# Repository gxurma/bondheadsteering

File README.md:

# bondheadsteering
App to steer a heated bondhead

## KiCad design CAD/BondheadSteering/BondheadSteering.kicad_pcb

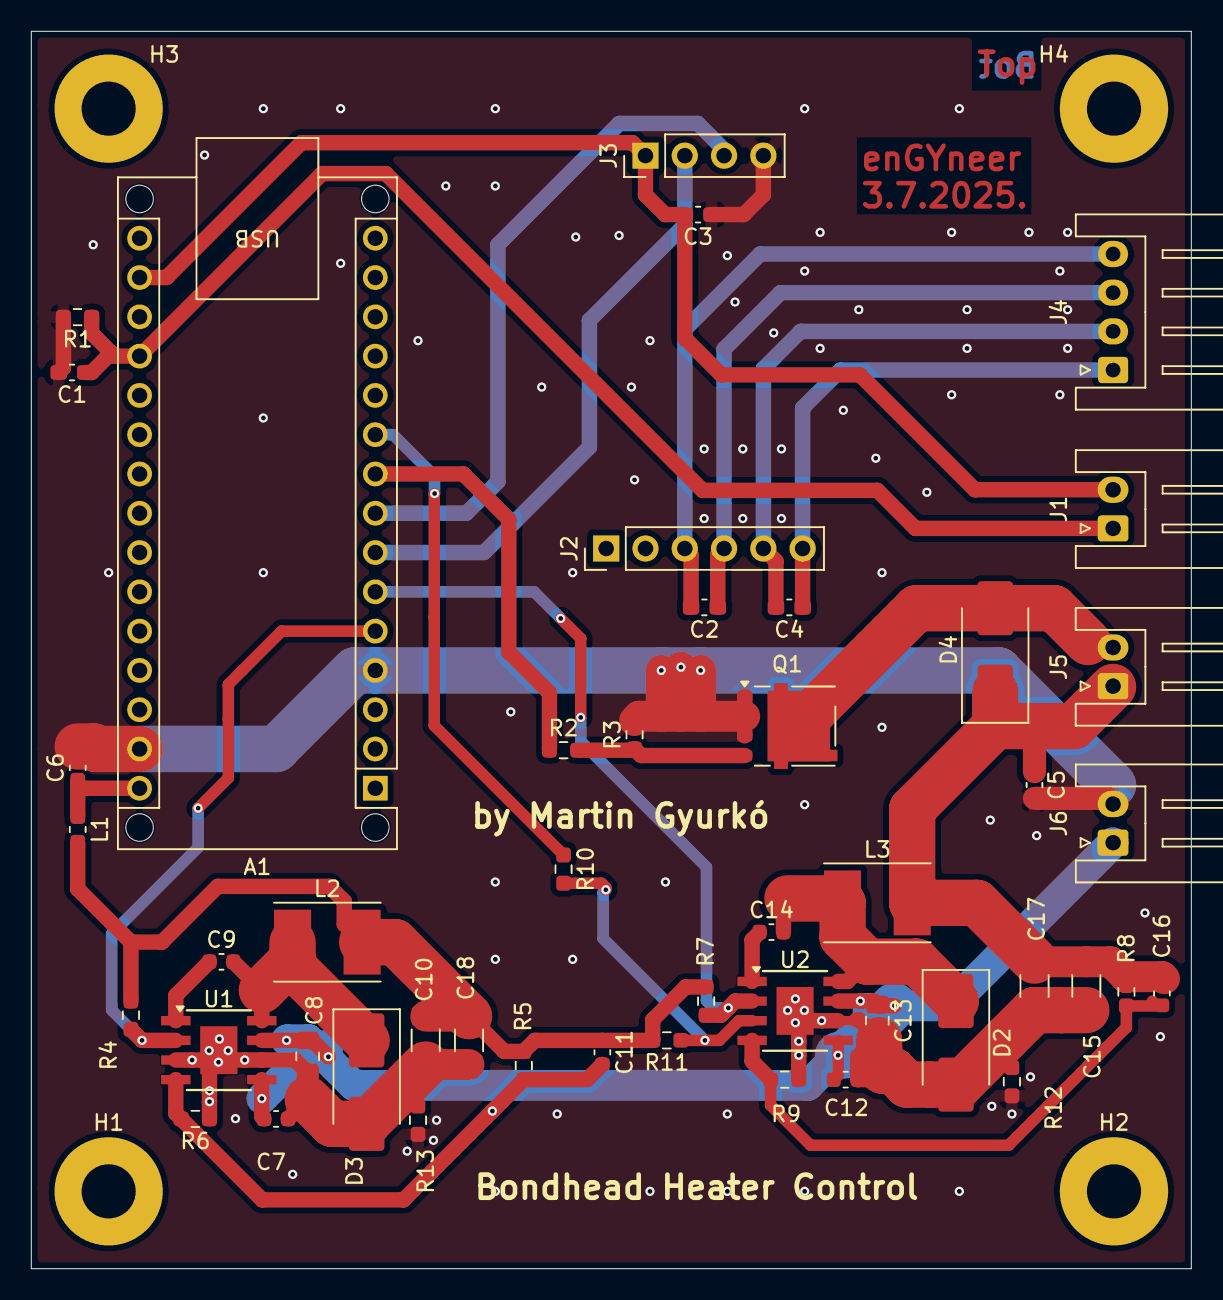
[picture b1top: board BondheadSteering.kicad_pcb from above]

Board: 2 copper layers, 75.0 x 80.0 mm, 51 parts (0 on the bottom side), 28 nets.

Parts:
A1: Arduino_Nano_RP2040_Connect; Arduino_Nano_WithMountingHoles
C1, C2, C3, C4, C5, C6: 1u; C_0603_1608Metric_Pad1.08x0.95mm_HandSolder
C7, C9, C12, C14: 100n; C_0603_1608Metric
C8, C13: 10u; C_0805_2012Metric_Pad1.18x1.45mm_HandSolder
C10, C15, C17, C18: 47u; C_1206_3216Metric_Pad1.33x1.80mm_HandSolder
C11, C16: 150p; C_0603_1608Metric
D2, D3, D4: STPS3L60U; D_SMB_Handsoldering
H1, H2, H3, H4: MountingHole; MountingHole_3.5mm_Pad
J1, J5, J6: Conn_01x02_Pin; JST_XH_S2B-XH-A_1x02_P2.50mm_Horizontal
J2: Conn_01x06_Socket; PinHeader_1x06_P2.54mm_Vertical
J3: Conn_01x04_Socket; PinHeader_1x04_P2.54mm_Vertical
J4: Conn_01x04_Pin; JST_XH_S4B-XH-A_1x04_P2.50mm_Horizontal
L1: 1uH; L_0603_1608Metric_Pad1.05x0.95mm_HandSolder
L2, L3: 10u; L_Taiyo-Yuden_NR-50xx_HandSoldering
Q1: AP90N02NF NMOS; ONSemi_SO-8FL_488AA
R1: 1961R; R_0603_1608Metric_Pad0.98x0.95mm_HandSolder
R2, R10: 100R; R_0603_1608Metric_Pad0.98x0.95mm_HandSolder
R3, R5, R8, R11: 10k; R_0603_1608Metric_Pad0.98x0.95mm_HandSolder
R4, R7: 47k; R_0603_1608Metric_Pad0.98x0.95mm_HandSolder
R6: 3160; R_0603_1608Metric_Pad0.98x0.95mm_HandSolder
R9: 1100; R_0603_1608Metric_Pad0.98x0.95mm_HandSolder
R12, R13: 0R; R_0603_1608Metric_Pad0.98x0.95mm_HandSolder
U1, U2: ST1S14PHR; TI_SO-PowerPAD-8

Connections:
+5V: C10.1, C11.1, C18.1, L1.2, L2.2, R4.1, R5.2, R7.1, R11.2
+12V: C5.1, C15.1, C16.1, C17.1, D4.1 (K), J5.1, L3.2, R8.2
+24V: C7.1, C8.1, C12.1, C13.1, J6.1, U1.5 (EN2), U1.7 (VIN), U2.5 (EN2), U2.7 (VIN)
/3V3: A1.17 (3V3), C3.2, J1.2, J3.1
/Boot5: C9.1, U1.1 (BOOT)
/Boot12: C14.1, U2.1 (BOOT)
/FB5: C11.2, R5.1, R6.2, U1.4 (FB)
/FB12: C16.2, R8.1, R9.2, U2.4 (FB)
/Switch5: C9.2, D3.1 (K), L2.1, U1.8 (SW)
/Switch12: C14.2, D2.1 (K), L3.1, U2.8 (SW)
/TempIn: A1.19 (A0), C1.1, J1.1, R1.1
GND1: C12.2, C13.2, C15.2, C17.2, D2.2 (A), R9.1, R12.2, U2.6 (GND), U2.9 (PADGND)
GND2: C7.2, C8.2, C10.2, C18.2, D3.2 (A), R6.1, R13.2, U1.3 (~EN1), U1.6 (GND), U1.9 (PADGND)
GNDD: A1.4 (GND), A1.29 (GND), C1.2, C3.1, C5.2, C6.2, J3.4, J6.2, Q1.1 (S), Q1.2 (S), Q1.3 (S), R1.2, R3.2, R12.1, R13.1
unnamed: A1.7 (D4), J3.2
unnamed: A1.8 (D5), J3.3
unnamed: A1.9 (D6), R2.1
unnamed: A1.10 (D7), R10.1
unnamed: A1.30 (VIN), C6.1, L1.1
unnamed: D4.2 (A), J5.2, Q1.5 (D)
unnamed: C2.2, J2.3, J4.4
unnamed: C2.1, J2.4, J4.3
unnamed: C4.2, J2.5, J4.2
unnamed: C4.1, J2.6, J4.1
unnamed: Q1.4 (G), R2.2, R3.1
unnamed: R10.2, R11.1, U2.3 (~EN1)
PGood5: A1.5 (D2), R4.2, U1.2 (PG)
PGood12: A1.6 (D3), R7.2, U2.2 (PG)

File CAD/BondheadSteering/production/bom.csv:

Designator,Footprint,Quantity,Value,LCSC Part #
A1,Arduino_Nano_WithMountingHoles,1,Arduino_Nano_RP2040_Connect,
"C1, C2, C3, C4, C5, C6",0603,6,1u,C1592
"C10, C15, C17, C18",1206,4,47u,C76659
"C11, C16",0603,2,150p,C1594
"C12, C14, C7, C9",0603,4,100n,C14663
"C13, C8",0805,2,10u,C440198
"D2, D3, D4",D_SMB_Handsoldering,3,STPS3L60U,C132769
"H1, H2, H3, H4",MountingHole_3.5mm_Pad,4,MountingHole,
"J1, J5, J6",JST_XH_S2B-XH-A_1x02_P2.50mm_Horizontal,3,Conn_01x02_Pin,C157931
J2,PinHeader_1x06_P2.54mm_Vertical,1,Conn_01x06_Socket,
J3,PinHeader_1x04_P2.54mm_Vertical,1,Conn_01x04_Socket,
J4,JST_XH_S4B-XH-A_1x04_P2.50mm_Horizontal,1,Conn_01x04_Pin,C157925
L1,0603,1,1uH,C22037
"L2, L3",L_Taiyo-Yuden_NR-50xx_HandSoldering,2,10u,C222896
Q1,ONSemi_SO-8FL_488AA,1,AP90N02NF NMOS,C3011254
R1,0603,1,1961R,C22854
"R10, R2",0603,2,100R,C22775
"R11, R3, R5, R8",0603,4,10k,C25804
"R12, R13",0603,2,0R,C15402
"R4, R7",0603,2,47k,C25819
R6,0603,1,3160,C22993
R9,0603,1,1100,C22764
"U1, U2",TI_SO-PowerPAD-8,2,ST1S14PHR,C84130

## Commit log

2025-05-30 app files
2025-05-31 Arduino sketch für den Heizer
2025-06-02 added threshold adjustment characteristic
2025-06-03 had to change heater indication so that it was working with the arduino plotter
2025-06-27 ble send
2025-06-29 added CAD for the control unit
2025-07-24 added lots of stuff. now working temp feedback courve
2025-07-24 now with threshold too
2025-07-24 now with serial parsing and force calibration
2025-07-28 added serial input for profile
2025-07-28 Added serial debugging with python
2025-07-28 Final delivery version 1
2025-11-14 new force calibration value for the flat cell
2025-11-16 Some minor changes to avoid crashing of app while scanning BLE
2025-11-16 Some CAD files
